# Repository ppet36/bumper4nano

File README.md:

# Bumper(Duino) for Arduino Nano

This is my modification of BumperDuino from Ardumower.de site for Arduino Nano instead of standalone ATMEGA328P. Some pins are remapped so modified MCU source is also available.

Original sources is available here https://github.com/Ardumower/ardumower

# Schematic

# PCB
PCB is designed as single sided with one wire jumper.

# Demo
Short demo is available here https://www.youtube.com/watch?v=Bmwo4UEfQBU

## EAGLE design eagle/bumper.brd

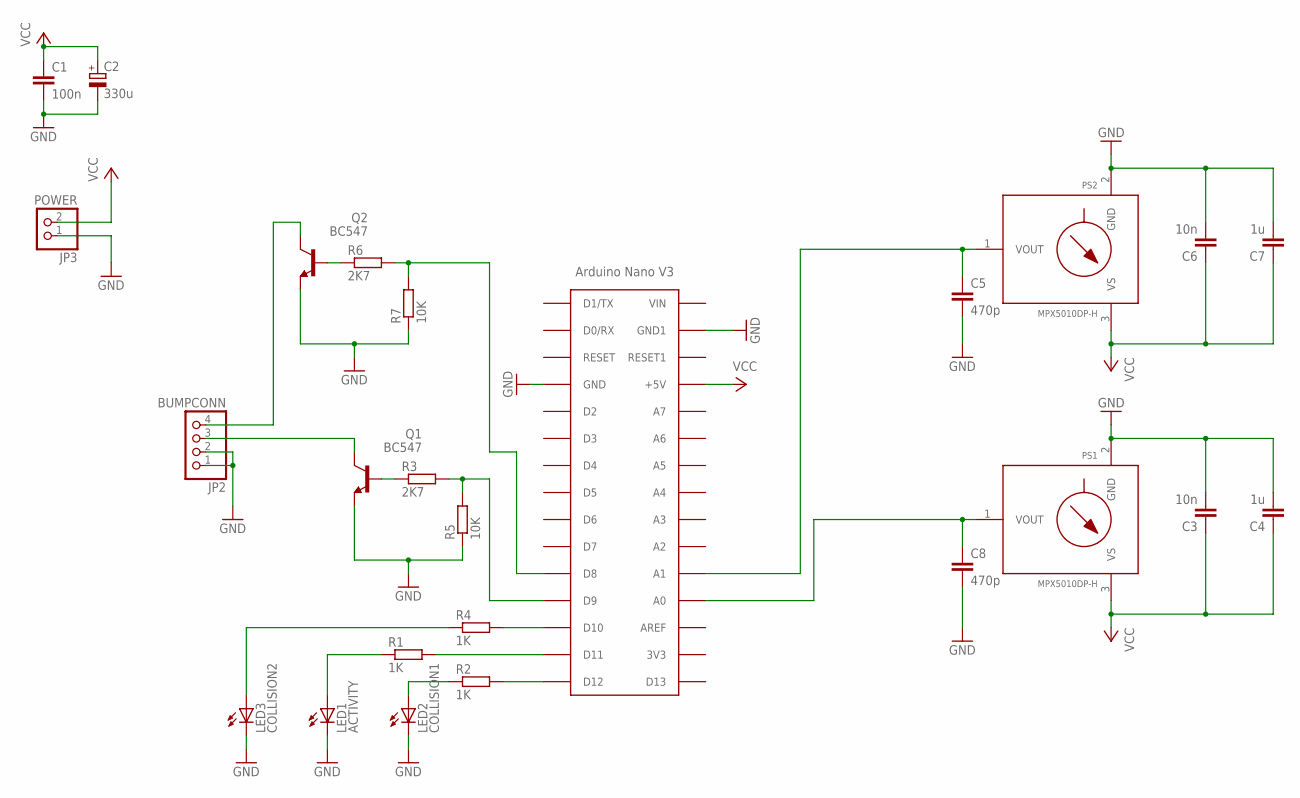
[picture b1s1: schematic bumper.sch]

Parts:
C1: 100n; C050-024X044
C2: 330u; E2,5-6E
C3, C6: 10n; C050-024X044
C4, C7: 1u; C050-035X075
C5, C8: 470p; C050-024X044
JP2: BUMPCONN; 1X04
JP3: POWER; 1X02
LED1: ACTIVITY; LED5MM
LED2: COLLISION1; LED5MM
LED3: COLLISION2; LED5MM
PS1, PS2: MPX5010DP-H; 867C-H
Q1, Q2: BC547; TO92-EBC
R1, R2, R4: 1K; 0204/7
R3, R6: 2K7; 0204/7
R5, R7: 10K; 0204/7
U$1: ARDUINONANO; PDIP-32

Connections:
GND: C1.2, C2.-, C3.2, C4.2, C5.2, C6.2, C7.2, C8.2, JP2.1, JP2.2, JP3.1, LED1.K (C), LED2.K (C), LED3.K (C), PS1.2 (GND), PS2.2 (GND), Q1.E, Q2.E, R5.1, R7.1, U$1.GND, U$1.GND1
unnamed: R1.2, U$1.D11
unnamed: LED1.A, R1.1
unnamed: R2.2, U$1.D12
unnamed: LED2.A, R2.1
unnamed: C8.1, PS1.1 (VOUT), U$1.A7 (A0)
unnamed: C5.1, PS2.1 (VOUT), U$1.A6 (A1)
unnamed: R3.2, R5.2, U$1.D9
unnamed: Q1.B, R3.1
unnamed: R6.2, R7.2, U$1.D8
unnamed: R4.2, U$1.D10
unnamed: JP2.3, Q1.C
unnamed: LED3.A, R4.1
unnamed: Q2.B, R6.1
unnamed: JP2.4, Q2.C
VCC: C1.1, C2.+, C3.1, C4.1, C6.1, C7.1, JP3.2, PS1.3 (VS), PS2.3 (VS), U$1.+5V

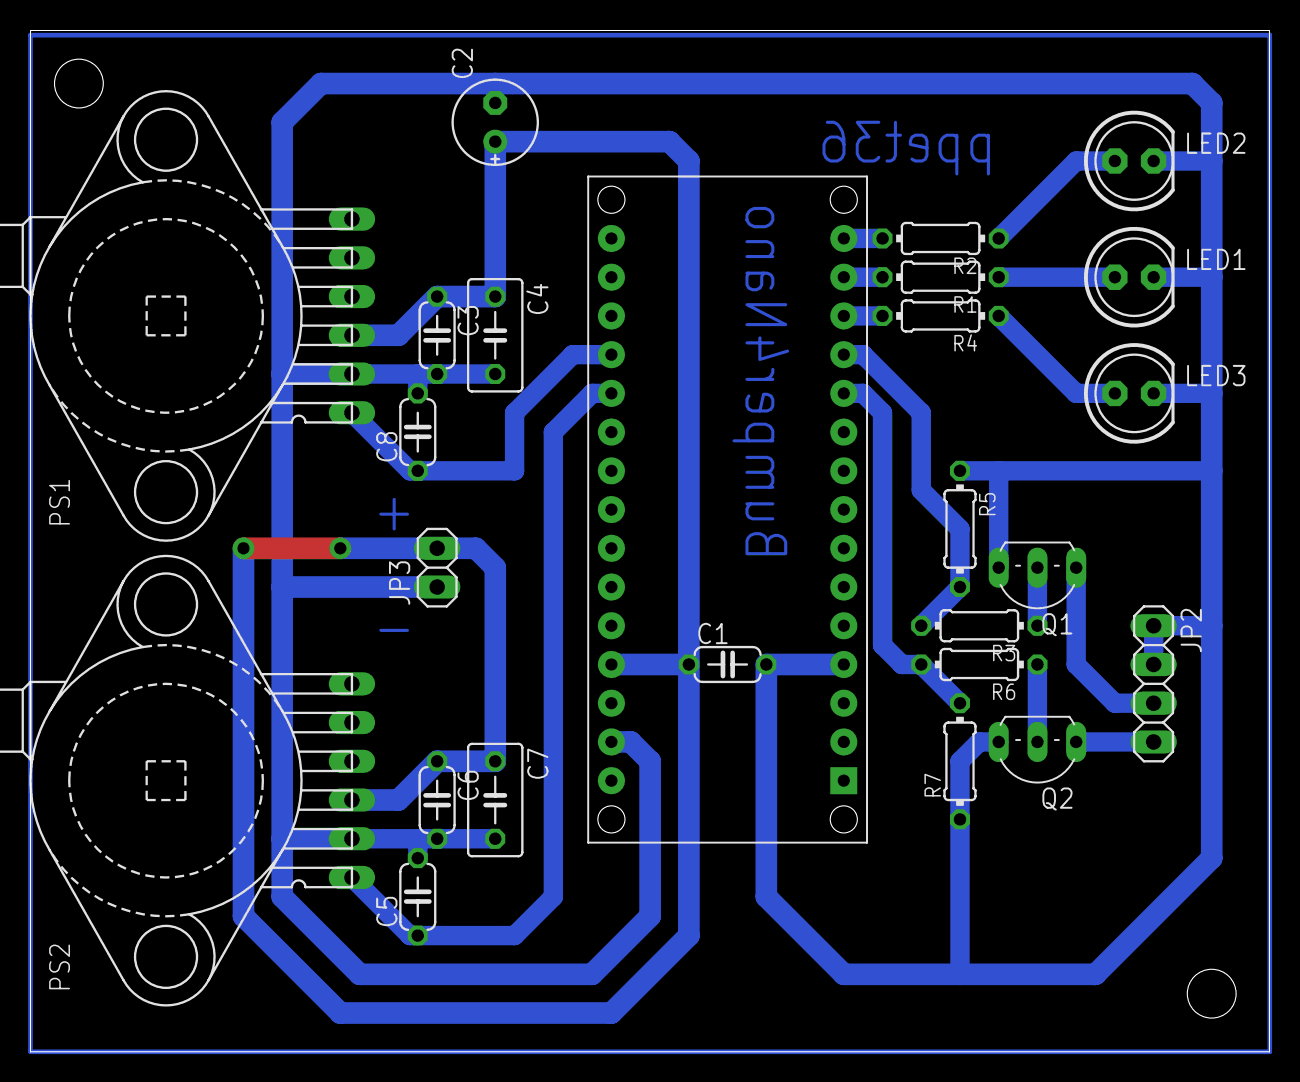
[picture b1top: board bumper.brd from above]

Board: 2 copper layers, 81.3 x 67.0 mm, 25 parts (0 on the bottom side), 16 nets.

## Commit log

2017-10-31 correction of reading second sensor
